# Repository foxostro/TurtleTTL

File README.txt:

TurtleTTL is an eight-bit microcomputer built from discrete logic ICs. The project also includes a CPU simulator, assembler, and a compiler for a new high-level programming language targeting the hardware.

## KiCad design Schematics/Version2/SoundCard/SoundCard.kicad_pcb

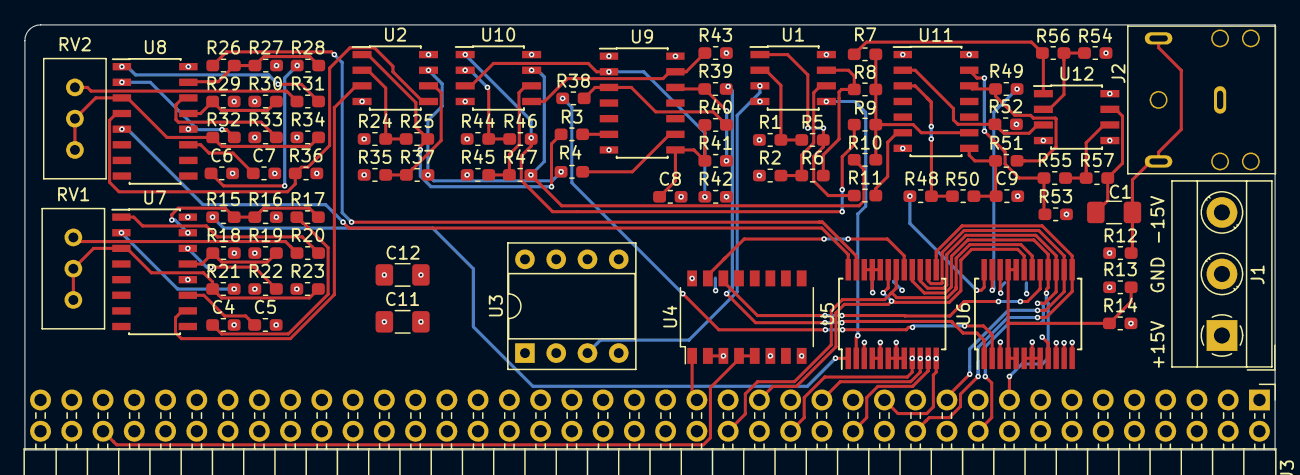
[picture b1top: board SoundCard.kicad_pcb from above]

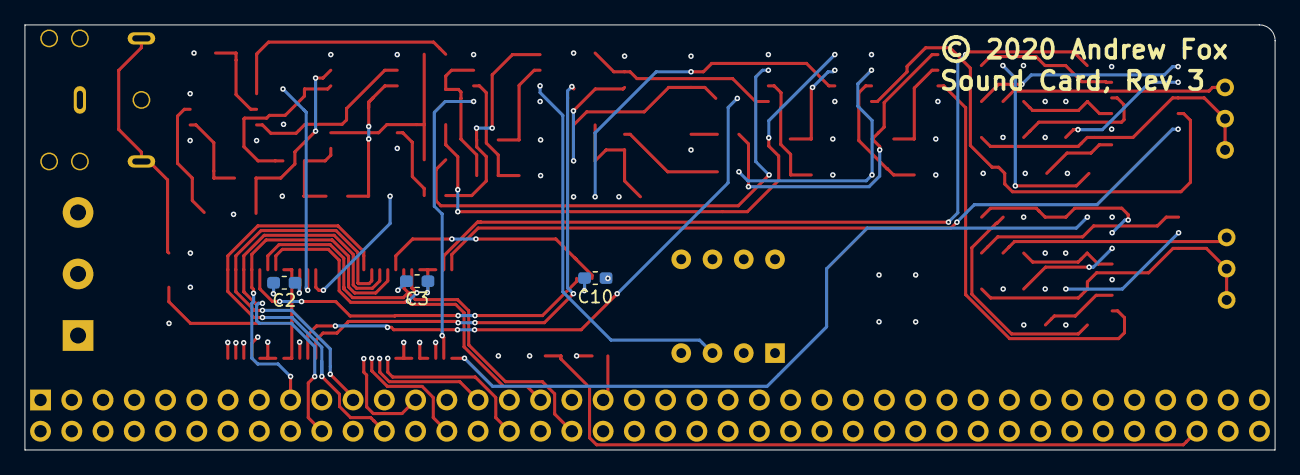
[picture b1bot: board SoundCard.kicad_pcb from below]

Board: 4 copper layers, 101.6 x 34.5 mm, 86 parts (3 on the bottom side), 79 nets.

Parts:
C1, C11, C12: 100µF; C_1206_3216Metric_Pad1.42x1.75mm_HandSolder
C2, C3, C10: 100nF; C_0603_1608Metric_Pad1.05x0.95mm_HandSolder
C4, C6: 10nF; C_0603_1608Metric_Pad1.05x0.95mm_HandSolder
C5, C7: 1nF; C_0603_1608Metric_Pad1.05x0.95mm_HandSolder
C8, C9: 5nF; C_0603_1608Metric_Pad1.05x0.95mm_HandSolder
J1: Screw_Terminal_01x03; TerminalBlock_MetzConnect_Type055_RT01503HDWU_1x03_P5.00mm_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
J2: AudioJack3; Jack_3.5mm_CUI_SJ1-3523N
J3: Conn; PinHeader_2x40_P2.54mm_Horizontal
R1, R2, R13, R24, R35, R44, R45, R54, R55: 10kΩ; R_0603_1608Metric_Pad1.05x0.95mm_HandSolder
R3, R4, R7, R8, R9, R10, R11, R42, R43, R52, R53: 47kΩ; R_0603_1608Metric_Pad1.05x0.95mm_HandSolder
R5, R6, R25, R46, R47, R56: 20kΩ; R_0603_1608Metric_Pad1.05x0.95mm_HandSolder
R12, R15, R26: 100kΩ; R_0603_1608Metric_Pad1.05x0.95mm_HandSolder
R14: 6.8kΩ; R_0603_1608Metric_Pad1.05x0.95mm_HandSolder
R16, R27: 360kΩ; R_0603_1608Metric_Pad1.05x0.95mm_HandSolder
R17, R28: 470Ω; R_0603_1608Metric_Pad1.05x0.95mm_HandSolder
R18, R29: 1.5MΩ; R_0603_1608Metric_Pad1.05x0.95mm_HandSolder
R19, R30: 47Ω; R_0603_1608Metric_Pad1.05x0.95mm_HandSolder
R20, R31: 24kΩ; R_0603_1608Metric_Pad1.05x0.95mm_HandSolder
R21, R32: 5.6kΩ; R_0603_1608Metric_Pad1.05x0.95mm_HandSolder
R22, R33: 1.8kΩ; R_0603_1608Metric_Pad1.05x0.95mm_HandSolder
R23, R34: 820Ω; R_0603_1608Metric_Pad1.05x0.95mm_HandSolder
R36: 51kΩ; R_0603_1608Metric_Pad1.05x0.95mm_HandSolder
R37, R40, R41, R50, R51: 2.4kΩ; R_0603_1608Metric_Pad1.05x0.95mm_HandSolder
R38, R39, R48, R49: 16kΩ; R_0603_1608Metric_Pad1.05x0.95mm_HandSolder
R57: 4.7kΩ; R_0603_1608Metric_Pad1.05x0.95mm_HandSolder
RV1, RV2: 10k; Potentiometer_Bourns_3386C_Horizontal
U1, U2, U10, U12: TL072; SOIC-8_3.9x4.9mm_P1.27mm
U3: PIC12F675-IP; DIP-8_W7.62mm_Socket
U4: 74AHCT138; SOP-16_4.4x10.4mm_P1.27mm
U5, U6: MAX505; SSOP-24_5.3x8.2mm_P0.65mm
U7, U8: AS3340; SOIC-16_3.9x9.9mm_P1.27mm
U9, U11: AS3360; SOIC-14_3.9x8.7mm_P1.27mm

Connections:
+15V: C11.1, J1.1, R16.2, R18.2, R27.2, R29.2, U1.8, U2.8, U7.16, U8.16, U9.14, U10.8, U11.14, U12.8
-15V: C12.2, J1.3, R23.1, R34.1, U1.4, U2.4, U9.7, U10.4, U11.7, U12.4
/Connector/AddressBus0: J3.33, U5.19, U6.19
/Connector/AddressBus1: J3.36, U5.18, U6.18
/Connector/AddressBus2: J3.37, U4.1
/Connector/DataBus0: J3.17, U5.16, U6.16
/Connector/DataBus1: J3.20, U5.15, U6.15
/Connector/DataBus2: J3.21, U5.14, U6.14
/Connector/DataBus3: J3.24, U5.13, U6.13
/Connector/DataBus4: J3.25, U5.12, U6.12
/Connector/DataBus5: J3.28, U5.11, U6.11
/Connector/DataBus6: J3.29, U5.10, U6.10
/Connector/DataBus7: J3.32, U5.9, U6.9
/Connector/~PI: J3.76, U4.4, U4.5
/DAC/VOUT0: U1.5, U5.2
/VCA2/CV1: R48.2, U6.24
/VCA2/CV2: R49.2, U6.23
/VCA2/VIN1: R11.2, U11.6
/VCA2/VIN2: R7.1, R8.1, R9.1, R10.1, U11.9
/VCA2/VOUT1: R7.2, R56.2, U12.1
/VCA2/VOUT2: C1.1, R57.2, U12.7
/VCA/CV1: R38.2, U6.2
/VCA/CV2: R39.2, U6.1
/VCA/VIN1: R3.1, U9.6
/VCA/VIN2: R4.1, U9.9
/VCA/VOUT1: R9.2, R46.2, U10.1
/VCA/VOUT2: R10.2, R47.2, U10.7
/VCO-Pulse/FrequencyCV: R26.1, U5.23
/VCO-Pulse/PWMCV: U5.24, U8.5
/VCO-Pulse/PulseOut: R4.2, R37.2, U2.7
/VCO-Triangle/CV: R15.1, U5.1
/VCO-Triangle/TriangleOut: R3.2, R25.2, U2.1
GND: C2.2, C3.2, C4.2, C5.2, C6.2, C7.2, C8.2, C9.2, C10.2, C11.2, C12.1, J1.2, J2.S, J3.2, J3.3, J3.6, J3.7, J3.10, J3.11, J3.14, J3.15, J3.18, J3.19, J3.22, J3.23, J3.26, J3.27, J3.30, J3.31, J3.34, J3.35, J3.38, J3.39, J3.42, J3.43, J3.46, J3.47, J3.50, J3.51, J3.54, J3.55, J3.58, J3.59, J3.62, J3.63, J3.66, J3.67, J3.70, J3.71, J3.74, J3.75, J3.78, J3.79, R1.1, R2.1, R12.2, R14.2, R19.1, R22.1, R24.1, R30.1, R33.1, R35.1, R36.2, R42.2, R43.2, R44.1, R45.1, R52.2, R53.2, R54.1, U3.8, U4.2, U4.3, U4.8, U5.3, U5.6, U5.7, U5.8, U6.3, U6.6, U6.7, U6.8, U7.12, U8.12, U9.1, U11.1, U12.5
unnamed: C1.2, J2.R, J2.T, R12.1
unnamed: C4.1, R17.1
unnamed: C5.1, U7.11
unnamed: C6.1, R28.1
unnamed: C7.1, U8.11
unnamed: C8.1, R40.1, R41.1, U9.8
unnamed: C9.1, R50.1, R51.1, U11.8
unnamed: R1.2, R5.1, U1.2
unnamed: R2.2, R6.1, U1.6
unnamed: R6.2, R8.2, U1.7
unnamed: R5.2, R11.1, U1.1
unnamed: R13.2, R14.1, U6.4, U6.5, U6.20, U6.21
unnamed: R15.2, R16.1, R17.2, U7.15
unnamed: R18.1, R19.2, U7.13
unnamed: R20.1, RV1.1
unnamed: R20.2, U7.1
unnamed: R21.1, R23.2, RV1.2, RV1.3, U7.3
unnamed: R21.2, U7.2
unnamed: R22.2, U7.14
unnamed: R24.2, R25.1, U2.2
unnamed: R26.2, R27.1, R28.2, U8.15
unnamed: R29.1, R30.2, U8.13
unnamed: R31.1, RV2.1
unnamed: R31.2, U8.1
unnamed: R32.1, R34.2, RV2.2, RV2.3, U8.3
unnamed: R32.2, U8.2
unnamed: R33.2, U8.14
unnamed: R35.2, R37.1, U2.6
unnamed: R36.1, U2.5, U8.4
unnamed: R38.1, R40.2, U9.3
unnamed: R39.1, R41.2, U9.12
unnamed: R42.1, U9.2, U10.3
unnamed: R43.1, U9.13, U10.5
unnamed: R44.2, R46.1, U10.2
unnamed: R45.2, R47.1, U10.6
unnamed: R48.1, R50.2, U11.3
unnamed: R49.1, R51.2, U11.12
unnamed: R52.1, U11.2, U12.3
unnamed: R53.1, R55.1, U11.13
unnamed: R54.2, R56.1, U12.2
unnamed: R55.2, R57.1, U12.6
unnamed: U1.3, U3.3
unnamed: U2.3, U7.10
unnamed: U4.14, U6.17
unnamed: U4.15, U5.17
VCC: C2.1, C3.1, C10.1, J3.1, J3.4, J3.5, J3.8, J3.9, J3.12, J3.13, J3.16, J3.73, J3.77, J3.80, R13.1, U3.1, U4.6, U4.16, U5.4, U5.5, U5.20, U5.21, U5.22, U6.22

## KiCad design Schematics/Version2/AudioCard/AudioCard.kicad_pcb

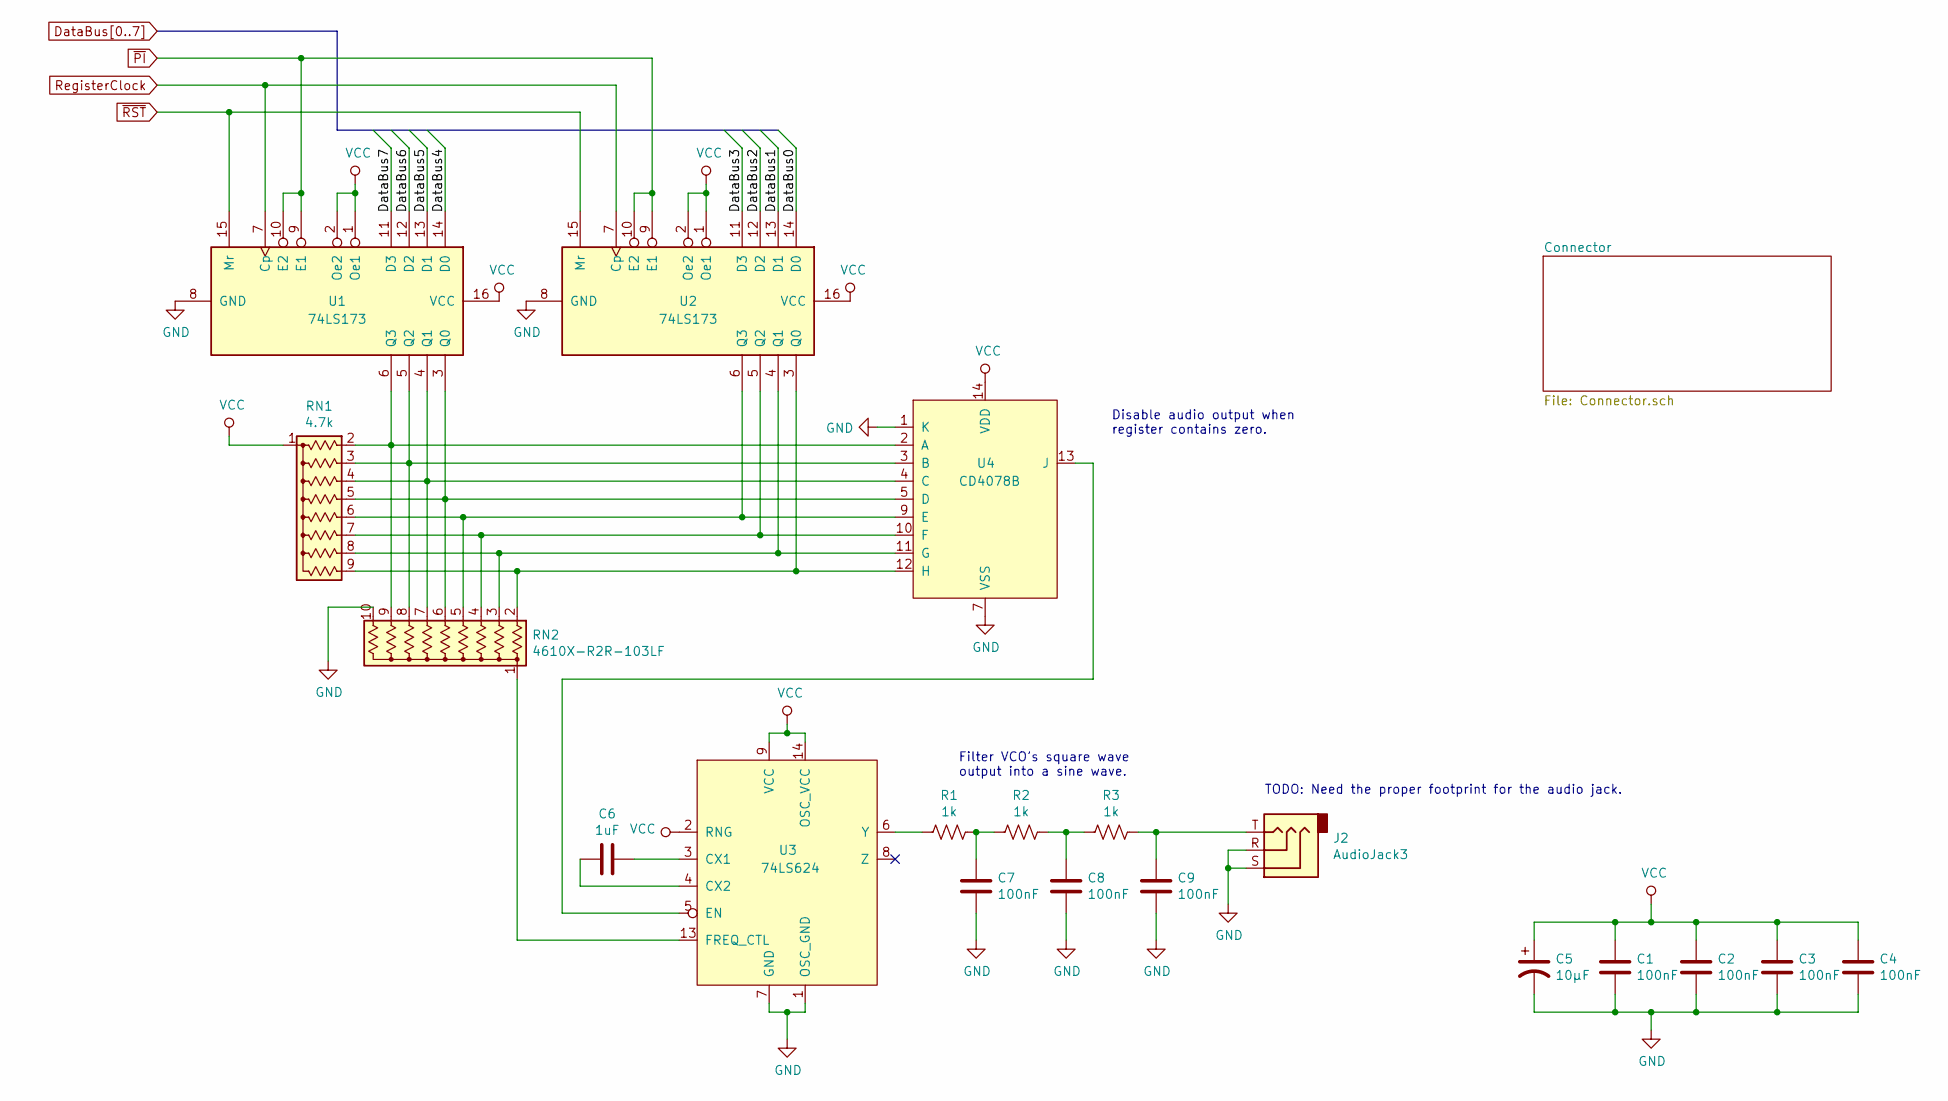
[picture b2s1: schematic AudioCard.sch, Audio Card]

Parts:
C1, C2, C3, C4, C7, C8, C9: 100nF; C_Disc_D4.3mm_W1.9mm_P5.00mm
C5: 10µF; CP_Radial_D5.0mm_P2.00mm
C6: 1uF; C_Disc_D4.3mm_W1.9mm_P5.00mm
J2: AudioJack3; Jack_3.5mm_CUI_SJ1-3533NG_Horizontal
R1, R2, R3: 1k; R_Axial_DIN0207_L6.3mm_D2.5mm_P7.62mm_Horizontal
RN1: 4.7k; R_Array_SIP9
RN2: 4610X-R2R-103LF; R_Array_SIP10
U1, U2: 74LS173; DIP-16_W7.62mm_Socket
U3: 74LS624; DIP-14_W7.62mm_Socket
U4: CD4078B; DIP-14_W7.62mm_Socket

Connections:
DataBus0: U2.14 (D0); also elsewhere on the board
DataBus1: U2.13 (D1); also elsewhere on the board
DataBus2: U2.12 (D2); also elsewhere on the board
DataBus3: U2.11 (D3); also elsewhere on the board
DataBus4: U1.14 (D0); also elsewhere on the board
DataBus5: U1.13 (D1); also elsewhere on the board
DataBus6: U1.12 (D2); also elsewhere on the board
DataBus7: U1.11 (D3); also elsewhere on the board
GND: C1.2, C2.2, C3.2, C4.2, C5.2, C7.2, C8.2, C9.2, J2.R, J2.S, RN2.10 (R9), U1.8 (GND), U2.8 (GND), U3.1 (OSC_GND), U3.7 (GND), U4.1 (K), U4.7 (VSS); also elsewhere on the board
unnamed: C6.1, U3.3 (CX1)
unnamed: C6.2, U3.4 (CX2)
unnamed: C7.1, R1.1, R2.2
unnamed: C8.1, R2.1, R3.2
unnamed: C9.1, J2.T, R3.1
unnamed: R1.2, U3.6 (Y)
unnamed: RN1.2 (R1), RN2.9 (R8), U1.6 (Q3), U4.2 (A)
unnamed: RN1.3 (R2), RN2.8 (R7), U1.5 (Q2), U4.3 (B)
unnamed: RN1.4 (R3), RN2.7 (R6), U1.4 (Q1), U4.4 (C)
unnamed: RN1.5 (R4), RN2.6 (R5), U1.3 (Q0), U4.5 (D)
unnamed: RN1.6 (R5), RN2.5 (R4), U2.6 (Q3), U4.9 (E)
unnamed: RN1.7 (R6), RN2.4 (R3), U2.5 (Q2), U4.10 (F)
unnamed: RN1.8 (R7), RN2.3 (R2), U2.4 (Q1), U4.11 (G)
unnamed: RN1.9 (R8), RN2.2 (R1), U2.3 (Q0), U4.12 (H)
unnamed: RN2.1 (common), U3.13 (FREQ_CTL)
unnamed: U3.5 (EN), U4.13 (J)
RegisterClock: U1.7 (Cp), U2.7 (Cp); also elsewhere on the board
VCC: C1.1, C2.1, C3.1, C4.1, C5.1, RN1.1 (common), U1.1 (Oe1), U1.2 (Oe2), U1.16 (VCC), U2.1 (Oe1), U2.2 (Oe2), U2.16 (VCC), U3.2 (RNG), U3.9 (VCC), U3.14 (OSC_VCC), U4.14 (VDD); also elsewhere on the board
~PI: U1.9 (E1), U1.10 (E2), U2.9 (E1), U2.10 (E2); also elsewhere on the board
~RST: U1.15 (Mr), U2.15 (Mr); also elsewhere on the board

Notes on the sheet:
Disable audio output when register contains zero.
Filter VCO’s square wave output into a sine wave.
TODO: Need the proper footprint for the audio jack.

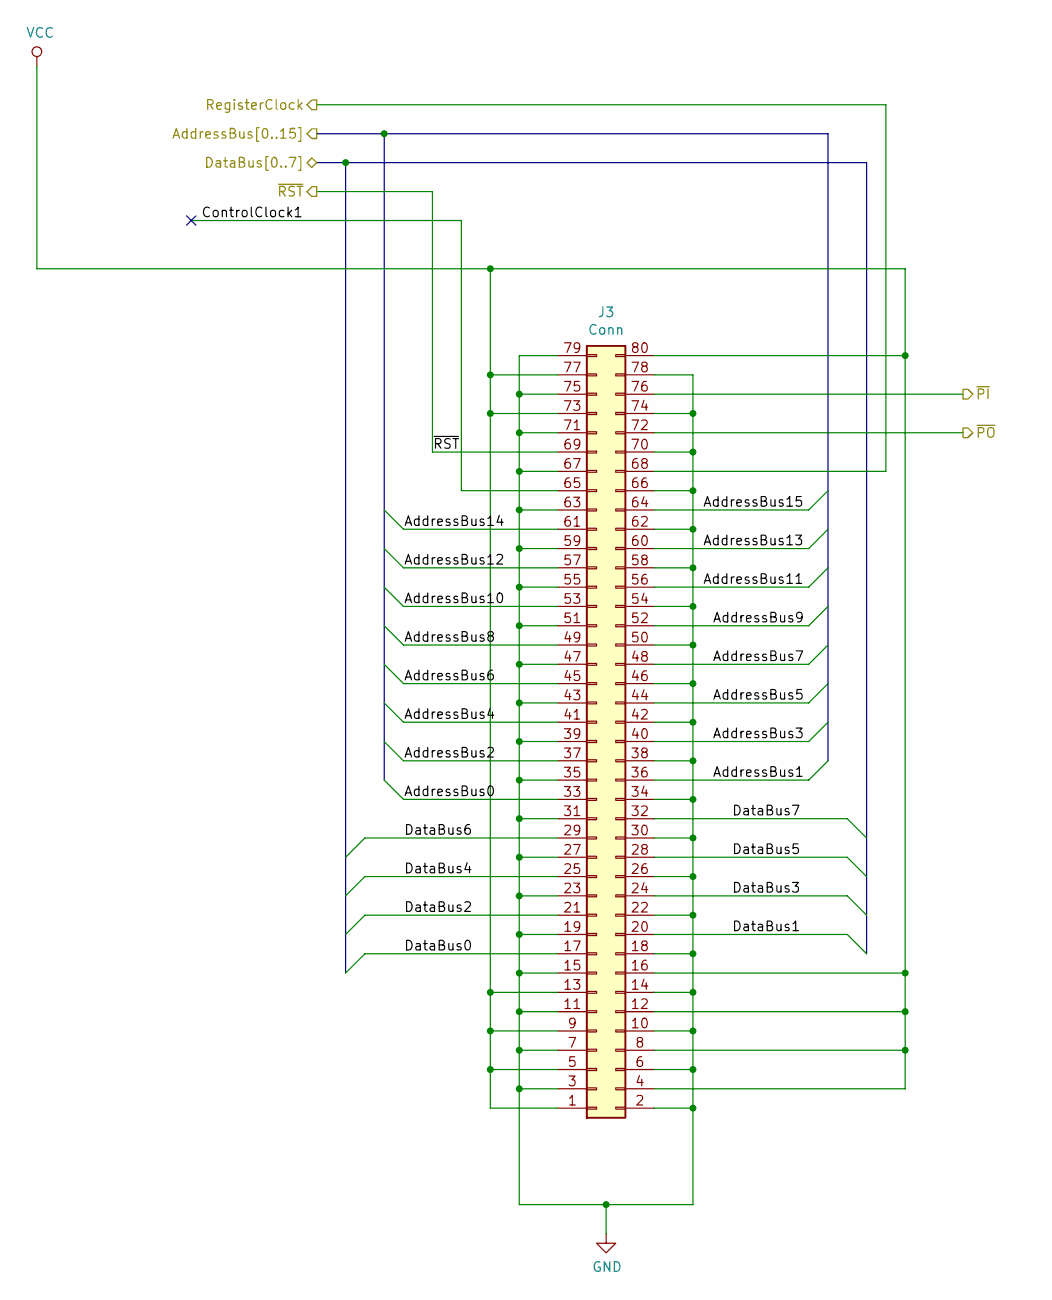
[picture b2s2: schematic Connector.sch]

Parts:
J3: Conn; PinHeader_2x40_P2.54mm_Horizontal

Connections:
unnamed: J3.1, J3.4, J3.5, J3.8, J3.9, J3.12, J3.13, J3.16, J3.73, J3.77, J3.80
unnamed: J3.2, J3.3, J3.6, J3.7, J3.10, J3.11, J3.14, J3.15, J3.18, J3.19, J3.22, J3.23, J3.26, J3.27, J3.30, J3.31, J3.34, J3.35, J3.38, J3.39, J3.42, J3.43, J3.46, J3.47, J3.50, J3.51, J3.54, J3.55, J3.58, J3.59, J3.62, J3.63, J3.66, J3.67, J3.70, J3.71, J3.74, J3.75, J3.78, J3.79

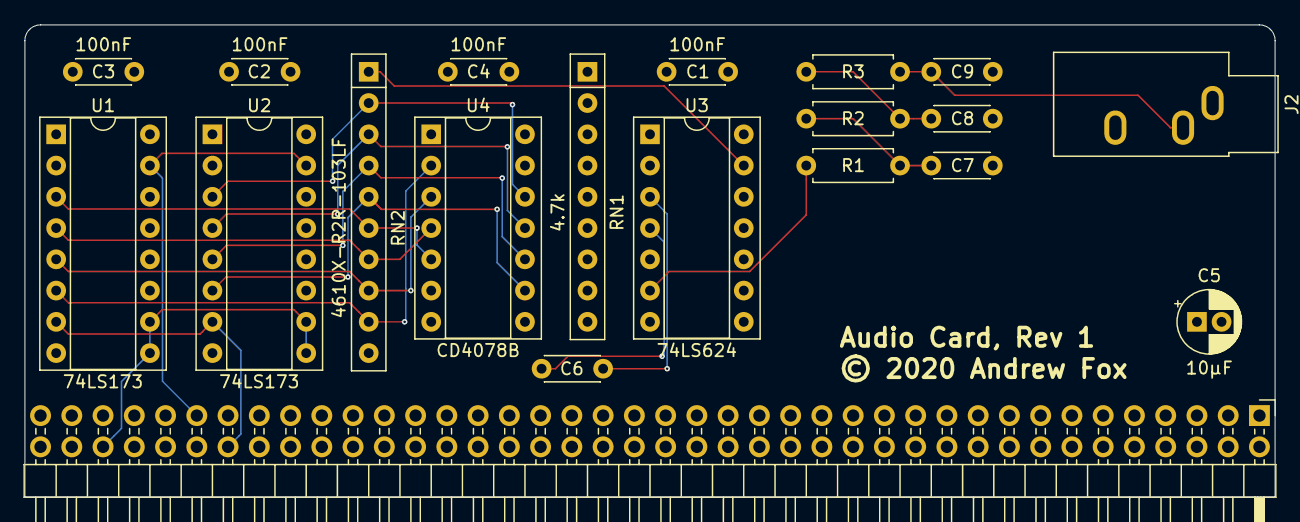
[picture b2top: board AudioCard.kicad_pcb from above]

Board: 4 copper layers, 101.6 x 38.4 mm, 20 parts (0 on the bottom side), 29 nets.

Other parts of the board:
J1: Conn; PinHeader_2x40_P2.54mm_Horizontal

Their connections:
DataBus0: J1.17; also elsewhere on the board
DataBus1: J1.20; also elsewhere on the board
DataBus2: J1.21; also elsewhere on the board
DataBus3: J1.24; also elsewhere on the board
DataBus4: J1.25; also elsewhere on the board
DataBus5: J1.28; also elsewhere on the board
DataBus6: J1.29; also elsewhere on the board
DataBus7: J1.32; also elsewhere on the board
GND: J1.2, J1.3, J1.6, J1.7, J1.10, J1.11, J1.14, J1.15, J1.18, J1.19, J1.22, J1.23, J1.26, J1.27, J1.30, J1.31, J1.34, J1.35, J1.38, J1.39, J1.42, J1.43, J1.46, J1.47, J1.50, J1.51, J1.54, J1.55, J1.58, J1.59, J1.62, J1.63, J1.66, J1.67, J1.70, J1.71, J1.74, J1.75, J1.78, J1.79; also elsewhere on the board
RegisterClock: J1.68; also elsewhere on the board
VCC: J1.1, J1.4, J1.5, J1.8, J1.9, J1.12, J1.13, J1.16, J1.73, J1.77, J1.80; also elsewhere on the board
~PI: J1.76; also elsewhere on the board
~RST: J1.69; also elsewhere on the board

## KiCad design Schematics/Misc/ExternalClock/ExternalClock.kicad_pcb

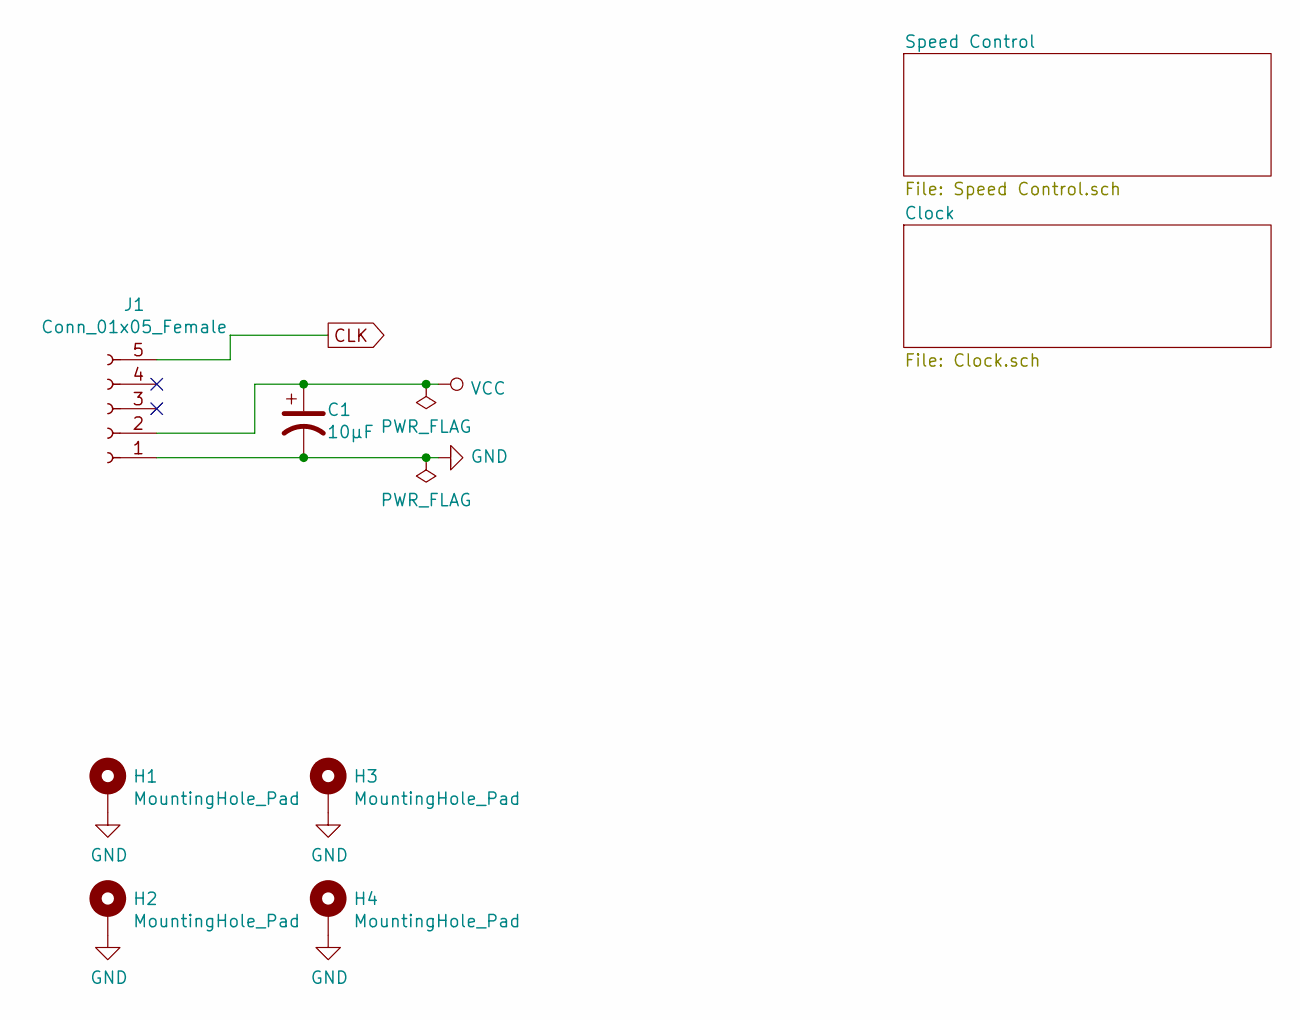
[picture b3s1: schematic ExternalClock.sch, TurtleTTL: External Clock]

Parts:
C1: 10µF; CP_Radial_D5.0mm_P2.00mm
H1, H2, H3, H4: MountingHole_Pad; MountingHole_3.2mm_M3_Pad
J1: Conn_01x05_Female; PinSocket_1x05_P2.54mm_Vertical

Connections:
CLK: J1.5; also elsewhere on the board
GND: C1.2, H1.1, H2.1, H3.1, H4.1, J1.1; also elsewhere on the board
VCC: C1.1, J1.2; also elsewhere on the board

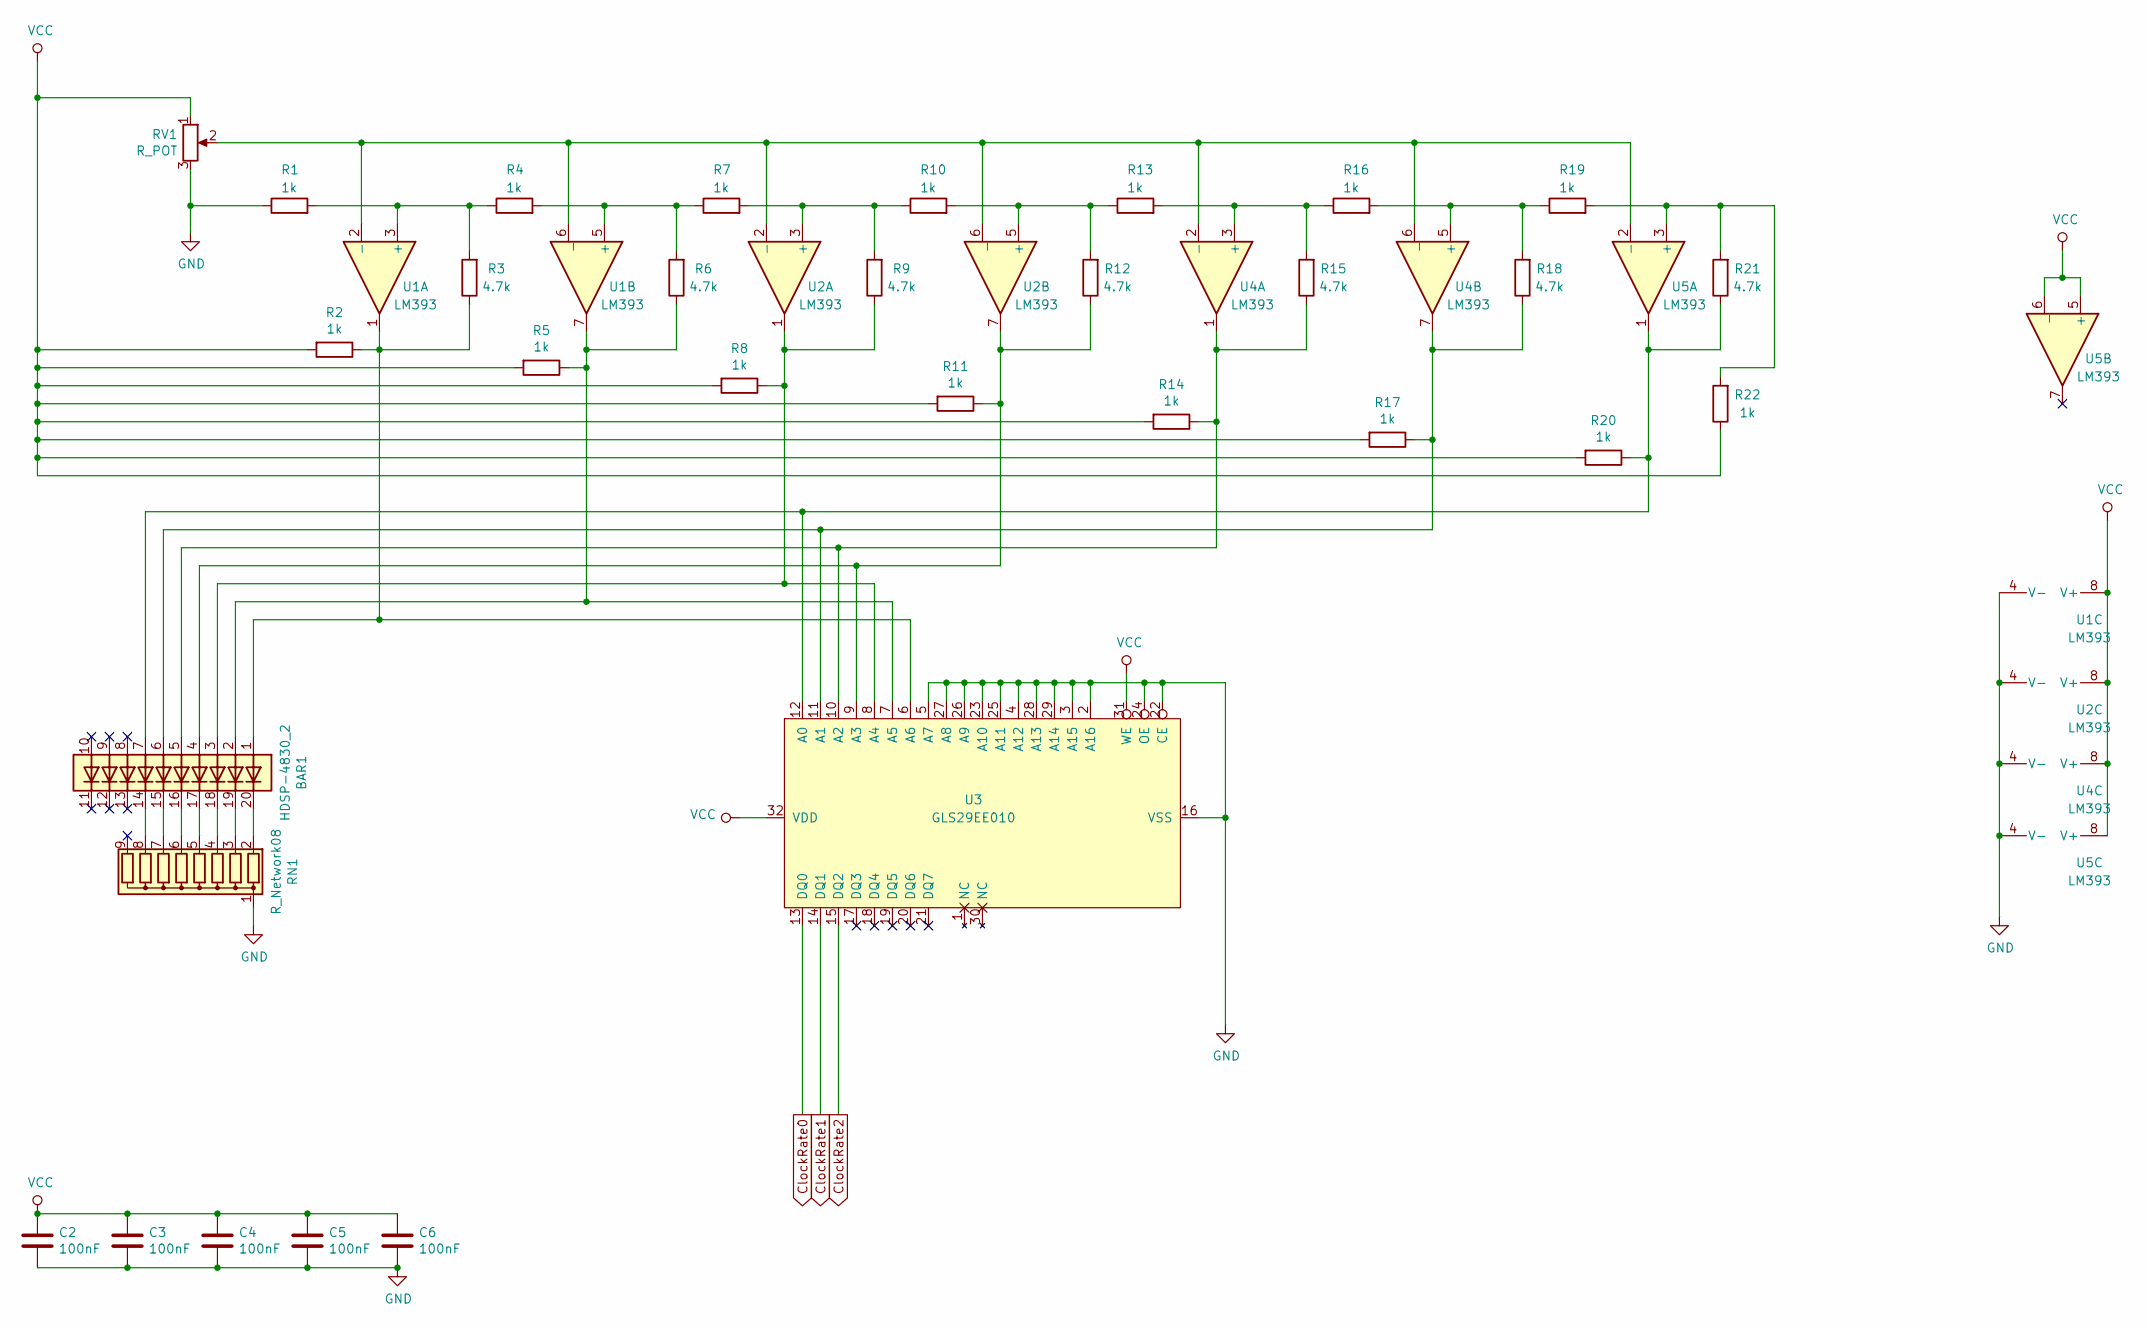
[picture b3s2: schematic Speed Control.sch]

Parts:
BAR1: HDSP-4830_2; HDSP-4830
C2, C3, C4, C5, C6: 100nF; C_Disc_D4.3mm_W1.9mm_P5.00mm
R1, R2, R4, R5, R7, R8, R10, R11, R13, R14, R16, R17, R19, R20, R22: 1k; R_Axial_DIN0207_L6.3mm_D2.5mm_P7.62mm_Horizontal
R3, R6, R9, R12, R15, R18, R21: 4.7k; R_Axial_DIN0207_L6.3mm_D2.5mm_P7.62mm_Horizontal
RN1: R_Network08; R_Array_SIP9
RV1: R_POT; Potentiometer_ACP_CA6-H2,5_Horizontal
U1, U2, U4, U5: LM393; DIP-8_W7.62mm
U3: GLS29EE010; DIP-32_W15.24mm_Socket

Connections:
ClockRate0: U3.13 (DQ0); also elsewhere on the board
ClockRate1: U3.14 (DQ1); also elsewhere on the board
ClockRate2: U3.15 (DQ2); also elsewhere on the board
GND: C2.2, C3.2, C4.2, C5.2, C6.2, R1.1, RN1.1 (common), RV1.3, U1.4 (V-), U2.4 (V-), U3.2 (A16), U3.3 (A15), U3.4 (A12), U3.5 (A7), U3.16 (VSS), U3.22 (CE), U3.23 (A10), U3.24 (OE), U3.25 (A11), U3.26 (A9), U3.27 (A8), U3.28 (A13), U3.29 (A14), U4.4 (V-), U5.4 (V-); also elsewhere on the board
unnamed: BAR1.1 (A), R2.1, R3.1, U1.1, U3.6 (A6)
unnamed: BAR1.2 (A), R5.1, R6.1, U1.7, U3.7 (A5)
unnamed: BAR1.3 (A), R8.1, R9.1, U2.1, U3.8 (A4)
unnamed: BAR1.4 (A), R11.1, R12.1, U2.7, U3.9 (A3)
unnamed: BAR1.5 (A), R14.1, R15.1, U3.10 (A2), U4.1
unnamed: BAR1.6 (A), R17.1, R18.1, U3.11 (A1), U4.7
unnamed: BAR1.7 (A), R20.1, R21.1, U3.12 (A0), U5.1
unnamed: BAR1.14 (K), RN1.8 (R7)
unnamed: BAR1.15 (K), RN1.7 (R6)
unnamed: BAR1.16 (K), RN1.6 (R5)
unnamed: BAR1.17 (K), RN1.5 (R4)
unnamed: BAR1.18 (K), RN1.4 (R3)
unnamed: BAR1.19 (K), RN1.3 (R2)
unnamed: BAR1.20 (K), RN1.2 (R1)
unnamed: R1.2, R3.2, R4.1, U1.3 (+)
unnamed: R4.2, R6.2, R7.1, U1.5 (+)
unnamed: R7.2, R9.2, R10.1, U2.3 (+)
unnamed: R10.2, R12.2, R13.1, U2.5 (+)
unnamed: R13.2, R15.2, R16.1, U4.3 (+)
unnamed: R16.2, R18.2, R19.1, U4.5 (+)
unnamed: R19.2, R21.2, R22.2, U5.3 (+)
unnamed: RV1.2, U1.2 (-), U1.6 (_), U2.2 (-), U2.6 (_), U4.2 (-), U4.6 (_), U5.2 (-)
VCC: C2.1, C3.1, C4.1, C5.1, C6.1, R2.2, R5.2, R8.2, R11.2, R14.2, R17.2, R20.2, R22.1, RV1.1, U1.8 (V+), U2.8 (V+), U3.31 (WE), U3.32 (VDD), U4.8 (V+), U5.5 (+), U5.6 (_), U5.8 (V+); also elsewhere on the board

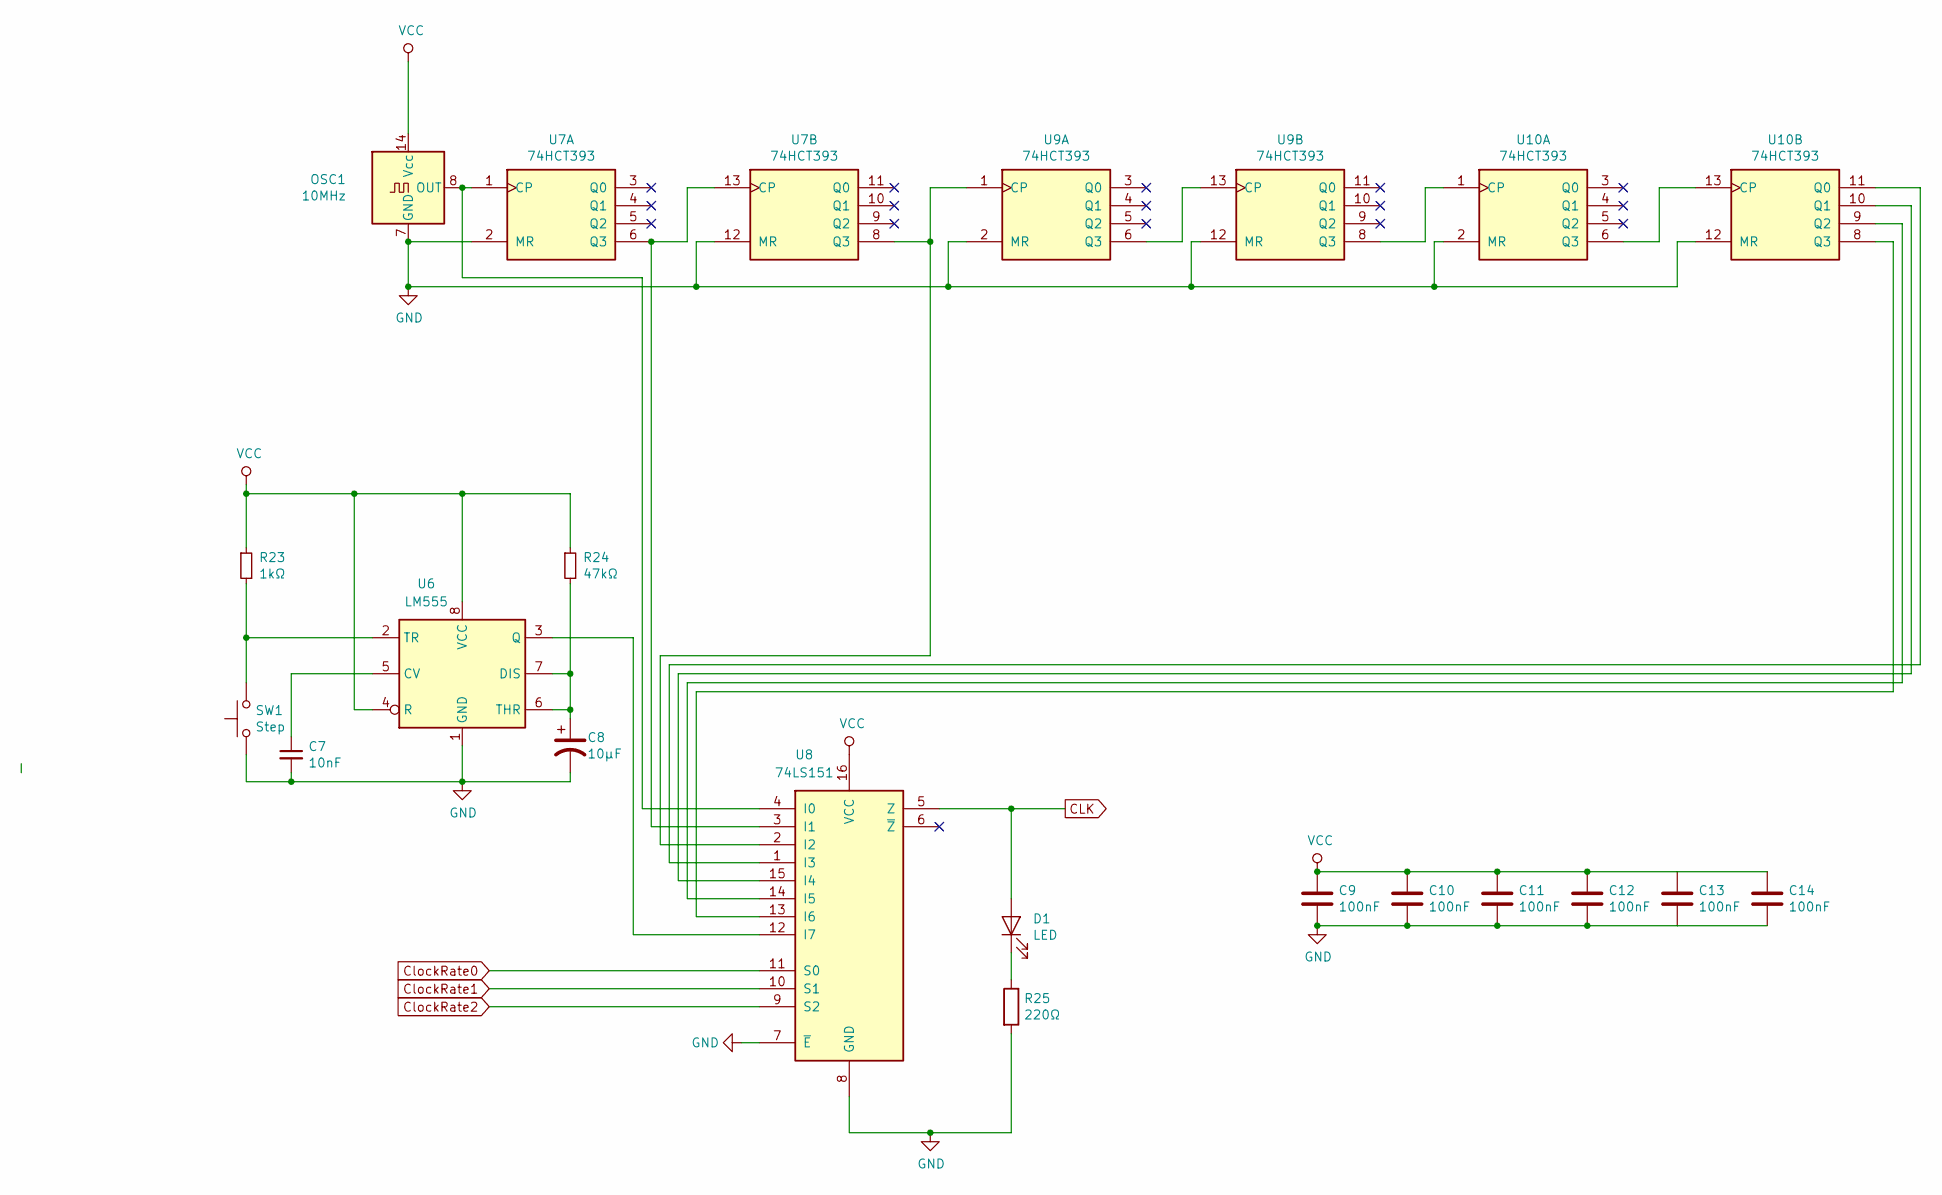
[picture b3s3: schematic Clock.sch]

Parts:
C7: 10nF; C_Disc_D4.3mm_W1.9mm_P5.00mm
C8: 10µF; CP_Radial_D5.0mm_P2.00mm
C9, C10, C11, C12, C13, C14: 100nF; C_Disc_D4.3mm_W1.9mm_P5.00mm
D1: LED; LED_D5.0mm
OSC1: 10MHz; Oscillator_DIP-14
R23: 1kΩ; R_Axial_DIN0207_L6.3mm_D2.5mm_P7.62mm_Horizontal
R24: 47kΩ; R_Axial_DIN0207_L6.3mm_D2.5mm_P7.62mm_Horizontal
R25: 220Ω; R_Axial_DIN0207_L6.3mm_D2.5mm_P7.62mm_Horizontal
SW1: Step; SW_PUSH_6mm_H5mm
U6: LM555; DIP-8_W7.62mm
U7, U9, U10: 74HCT393; DIP-14_W7.62mm
U8: 74LS151; DIP-16_W7.62mm

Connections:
CLK: D1.2 (A), U8.5 (Z); also elsewhere on the board
ClockRate0: U8.11 (S0); also elsewhere on the board
ClockRate1: U8.10 (S1); also elsewhere on the board
ClockRate2: U8.9 (S2); also elsewhere on the board
GND: C7.2, C8.2, C9.2, C10.2, C11.2, C12.2, C13.2, C14.2, OSC1.7 (GND), R25.2, SW1.1, U6.1 (GND), U7.2 (MR), U7.12 (MR), U8.7 (~E), U8.8 (GND), U9.2 (MR), U9.12 (MR), U10.2 (MR), U10.12 (MR); also elsewhere on the board
unnamed: C7.1, U6.5 (CV)
unnamed: C8.1, R24.2, U6.6 (THR), U6.7 (DIS)
unnamed: D1.1 (K), R25.1
unnamed: OSC1.8 (OUT), U7.1 (CP), U8.4 (I0)
unnamed: R23.2, SW1.2, U6.2 (TR)
unnamed: U6.3 (Q), U8.12 (I7)
unnamed: U7.8 (Q3), U8.2 (I2), U9.1 (CP)
unnamed: U7.6 (Q3), U7.13 (CP), U8.3 (I1)
unnamed: U9.6 (Q3), U9.13 (CP)
unnamed: U9.8 (Q3), U10.1 (CP)
unnamed: U8.13 (I6), U10.8 (Q3)
unnamed: U8.14 (I5), U10.9 (Q2)
unnamed: U8.15 (I4), U10.10 (Q1)
unnamed: U8.1 (I3), U10.11 (Q0)
unnamed: U10.6 (Q3), U10.13 (CP)
VCC: C9.1, C10.1, C11.1, C12.1, C13.1, C14.1, OSC1.14 (Vcc), R23.1, R24.1, U6.4 (R), U6.8 (VCC), U8.16 (VCC); also elsewhere on the board

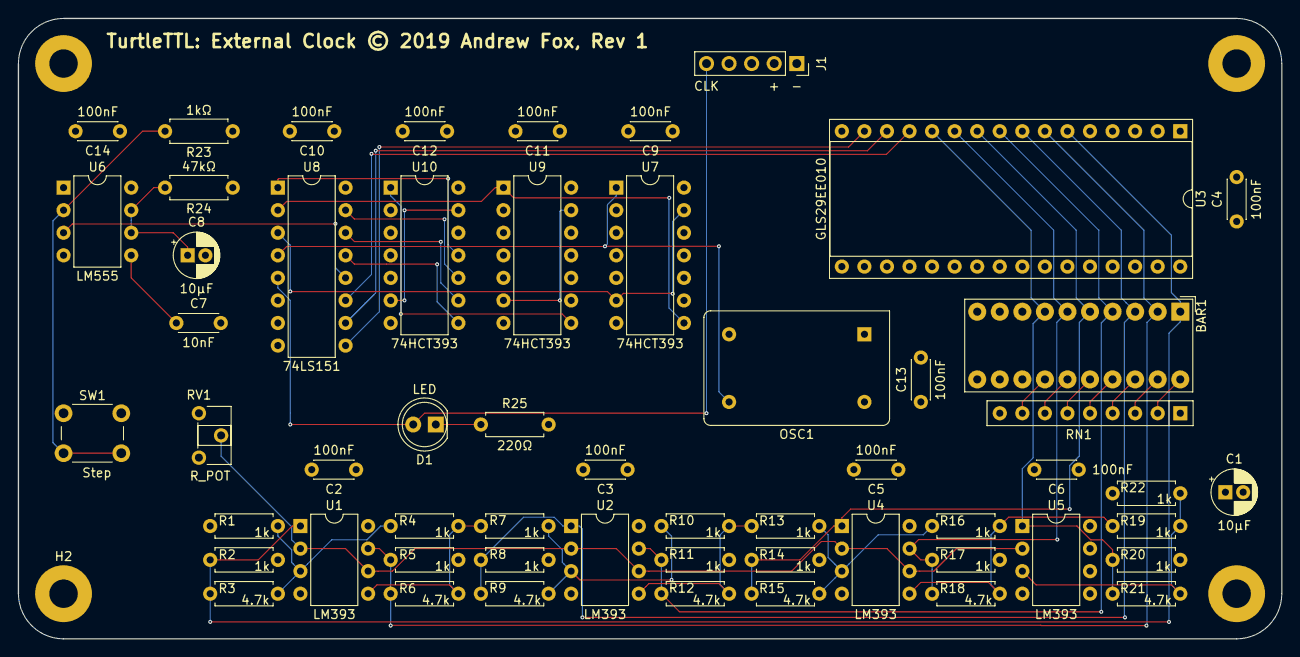
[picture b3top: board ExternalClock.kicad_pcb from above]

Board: 4 copper layers, 142.2 x 69.9 mm, 60 parts (0 on the bottom side), 43 nets.

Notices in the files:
Schematics/MainBoard/MainBoard.kicad_pcb:
TurtleTTL © 2019 Andrew Fox, Rev 1
Schematics/Misc/ExternalClock/ExternalClock.kicad_pcb:
TurtleTTL: External Clock © 2019 Andrew Fox, Rev 1
Schematics/RAMCard/RAMCard.kicad_pcb:
RAM Card © 2019 Andrew Fox, Rev 1
Schematics/SerialCard/SerialCard.kicad_pcb:
Serial Card © 2019 Andrew Fox, Rev 2
Schematics/Version1/ArduinoSerialCard/ArduinoSerialCard.kicad_pcb:
© 2019 Andrew Fox, Rev 3
Schematics/Version2/AudioCard/AudioCard.kicad_pcb:
© 2020 Andrew Fox
